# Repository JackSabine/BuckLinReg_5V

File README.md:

# Buck + Linear Regulator

Power supply for the Breadboard\_CPU.  This converter accepts input voltages 8 - 13 V and will output a regulated 5 V.

Tried to bodge a wire to measure a voltage without a testpoint...  Oops...

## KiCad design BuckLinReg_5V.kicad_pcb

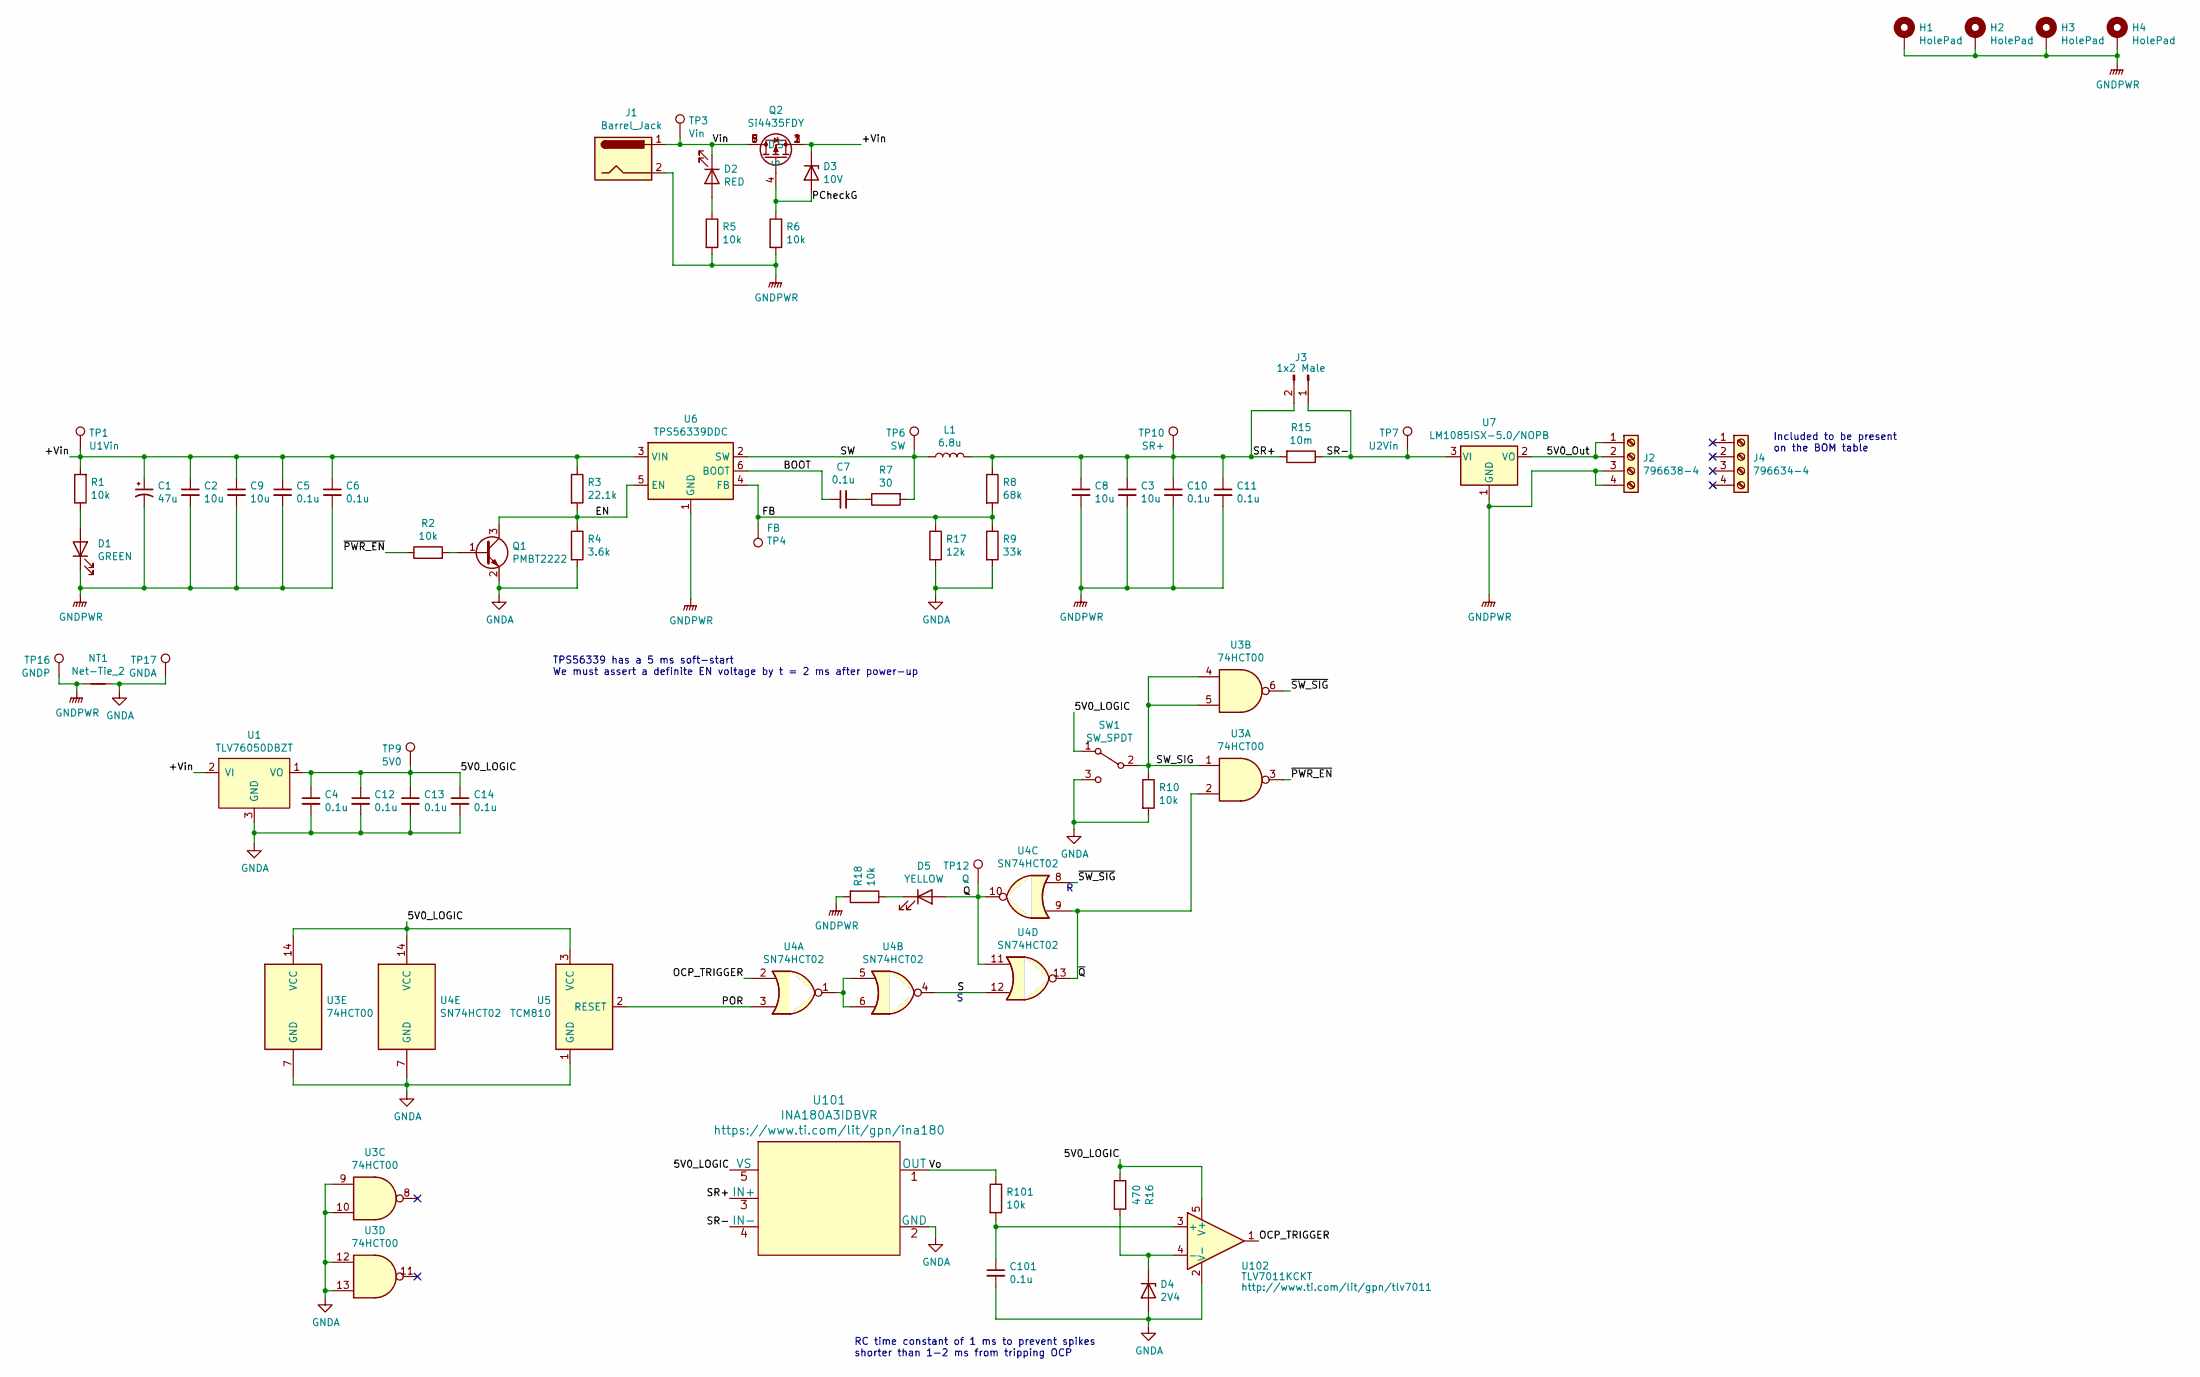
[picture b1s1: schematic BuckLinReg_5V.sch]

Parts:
C1: 47u; CP_Radial_D6.3mm_P2.50mm
C2, C3: 10u; C_1206_3216Metric_Pad1.33x1.80mm_HandSolder
C4, C6, C7, C11, C12, C13, C14, C101: 0.1u; C_0603_1608Metric_Pad1.08x0.95mm_HandSolder
C5, C10: 0.1u; C_0805_2012Metric_Pad1.18x1.45mm_HandSolder
C8, C9: 10u; C_1210_3225Metric_Pad1.33x2.70mm_HandSolder
D1: GREEN; D_1206_3216Metric_Pad1.42x1.75mm_HandSolder
D2: RED; D_1206_3216Metric_Pad1.42x1.75mm_HandSolder
D3: 10V; D_SOT-23_ANK
D4: 2V4; D_SOD-323_HandSoldering
D5: YELLOW; D_1206_3216Metric_Pad1.42x1.75mm_HandSolder
H1, H2, H3, H4: HolePad; ProjectBoxMountingHole_X001WPJR9N
J1: Barrel_Jack; BarrelJack_CUI_PJ-102AH_Horizontal
J2: 796638-4; 796636-4
J3: 1x2 Male; PinHeader_1x02_P2.54mm_Vertical
J4: 796634-4
L1: 6.8u; IHLP4040DZER6R8M8A
NT1: Net-Tie_2; NetShorter
Q1: PMBT2222; SOT-23_Handsoldering
Q2: Si4435FDY; SO-8_3.9x4.9mm_P1.27mm
R1, R2, R5, R6, R10, R18, R101: 10k; R_1206_3216Metric_Pad1.30x1.75mm_HandSolder
R3: 22.1k; R_1206_3216Metric_Pad1.30x1.75mm_HandSolder
R4: 3.6k; R_1206_3216Metric_Pad1.30x1.75mm_HandSolder
R7: 30; R_2010_5025Metric_Pad1.40x2.65mm_HandSolder
R8: 68k; R_1206_3216Metric_Pad1.30x1.75mm_HandSolder
R9: 33k; R_1206_3216Metric_Pad1.30x1.75mm_HandSolder
R15: 10m; R_1206_3216Metric_Pad1.30x1.75mm_HandSolder
R16: 470; R_1206_3216Metric_Pad1.30x1.75mm_HandSolder
R17: 12k; R_1206_3216Metric_Pad1.30x1.75mm_HandSolder
SW1: SW_SPDT; PinHeader_1x03_P2.54mm_Vertical
TP1: U1Vin; TestPoint_THTPad_D2.0mm_Drill1.0mm
TP3: Vin; TestPoint_THTPad_D2.0mm_Drill1.0mm
TP4: FB; TestPoint_THTPad_D2.0mm_Drill1.0mm
TP6: SW; TestPoint_THTPad_D2.0mm_Drill1.0mm
TP7: U2Vin; TestPoint_THTPad_D2.0mm_Drill1.0mm
TP9: 5V0; TestPoint_THTPad_D2.0mm_Drill1.0mm
TP10: SR+; TestPoint_THTPad_D2.0mm_Drill1.0mm
TP12: Q; TestPoint_THTPad_D2.0mm_Drill1.0mm
TP16: GNDP; TestPoint_THTPad_D2.0mm_Drill1.0mm
TP17: GNDA; TestPoint_THTPad_D2.0mm_Drill1.0mm
U1: TLV76050DBZT; SOT-23_Handsoldering
U3: 74HCT00; SOIC-14_3.9x8.7mm_P1.27mm
U4: SN74HCT02; SOIC-14_3.9x8.7mm_P1.27mm
U5: TCM810; SOT-23_Handsoldering
U6: TPS56339DDC; SOT-23-6
U7: LM1085ISX-5.0/NOPB; TO-263-3_TabPin2
U101: INA180A3IDBVR; SOT-23-5_HandSoldering
U102: TLV7011KCKT; SOT-23-5_HandSoldering

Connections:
/5V0_LOGIC: C4.1, C12.1, C13.1, C14.1, R16.1, SW1.1 (A), TP9.1, U1.1 (VO), U3.14 (VCC), U4.14 (VCC), U5.3 (VCC), U101.5 (VS), U102.5 (V+)
/5V0_Out: J2.1, J2.2, U7.2 (VO)
/+Vin: C1.1, C2.1, C5.1, C6.1, C9.1, D3.1 (K), Q2.1 (S), Q2.2 (S), Q2.3 (S), R1.2, R3.1, TP1.1, U1.2 (VI), U6.3 (VIN)
/BOOT: C7.1, U6.6 (BOOT)
/EN: Q1.3 (C), R3.2, R4.1, U6.5 (EN)
/FB: R8.2, R9.1, R17.1, TP4.1, U6.4 (FB)
/OCP_TRIGGER: U4.2, U102.1; also elsewhere on the board
/PCheckG: D3.2 (A), Q2.4 (G), R6.1
/POR: U4.3, U5.2 (RESET)
/Q: D5.2 (A), TP12.1, U4.10, U4.11
/S: U4.4, U4.12
/SR+: C3.1, C8.1, C10.1, C11.1, J3.2, L1.2, R8.1, R15.2, TP10.1, U101.3 (IN+)
/SR-: J3.1, R15.1, TP7.1, U7.3 (VI), U101.4 (IN-)
/SW: L1.1, R7.2, TP6.1, U6.2 (SW)
/SW_SIG: R10.1, SW1.2 (B), U3.1, U3.4, U3.5
/Vin: D2.1 (K), J1.1, Q2.5 (D), Q2.6 (D), Q2.7 (D), Q2.8 (D), TP3.1
/Vo: R101.1, U101.1 (OUT); also elsewhere on the board
/~PWR_EN: R2.1, U3.3
/~Q: U3.2, U4.9, U4.13
/~SW_SIG: U3.6, U4.8
GNDA: C4.2, C12.2, C13.2, C14.2, C101.2, D4.2 (A), NT1.2, Q1.2 (E), R4.2, R9.2, R10.2, R17.2, SW1.3 (C), TP17.1, U1.3 (GND), U3.7 (GND), U3.9, U3.10, U3.12, U3.13, U4.7 (GND), U5.1 (GND), U101.2 (GND), U102.2 (V-)
GNDPWR: C1.2, C2.2, C3.2, C5.2, C6.2, C8.2, C9.2, C10.2, C11.2, D1.1 (K), H1.1, H2.1, H3.1, H4.1, J1.2, J2.3, J2.4, NT1.1, R5.2, R6.2, R18.2, TP16.1, U6.1 (GND), U7.1 (GND)
unnamed: C7.2, R7.1
unnamed: C101.1, R101.2, U102.3 (+)
unnamed: D1.2 (A), R1.1
unnamed: D2.2 (A), R5.1
unnamed: D4.1 (K), R16.2, U102.4 (-)
unnamed: D5.1 (K), R18.1
unnamed: Q1.1 (B), R2.2
unnamed: U4.1, U4.5, U4.6

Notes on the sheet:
TPS56339 has a 5 ms soft-start We must assert a definite EN voltage by t = 2 ms after power-up
Included to be present on the BOM table
RC time constant of 1 ms to prevent spikes shorter than 1-2 ms from tripping OCP

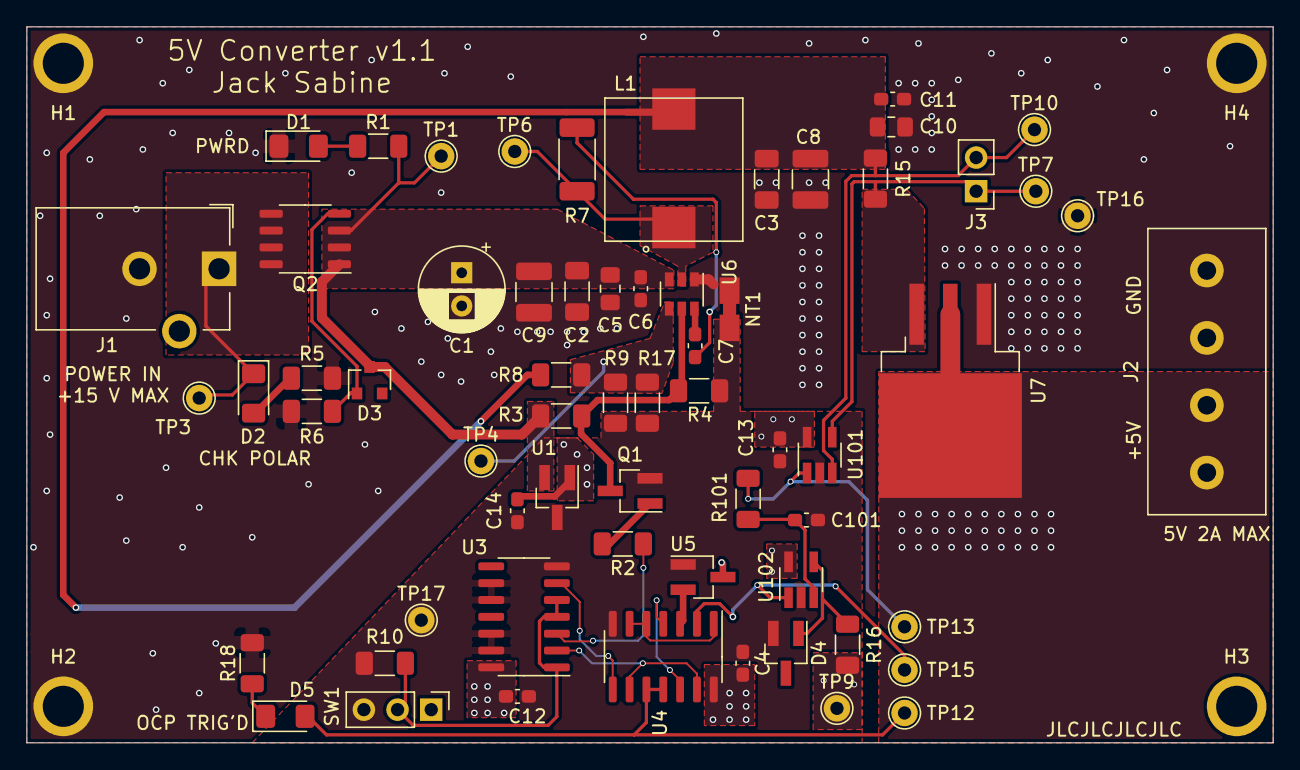
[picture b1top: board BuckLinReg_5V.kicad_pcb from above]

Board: 2 copper layers, 94.0 x 54.0 mm, 67 parts (0 on the bottom side), 30 nets.

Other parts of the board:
TP13: Iout; TestPoint_THTPad_D2.0mm_Drill1.0mm
TP15: OCPT; TestPoint_THTPad_D2.0mm_Drill1.0mm

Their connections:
/OCP_TRIGGER: TP15.1; also elsewhere on the board
/Vo: TP13.1; also elsewhere on the board

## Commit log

2021-02-05 Init
2021-02-06 Created .sch, selected parts, started PCB layout
2021-02-11 Added overcurrent protection circuit and assigned all MFPNs and footprints
2021-02-13 Two grounds: GNDA and pwrGND. Continued PCB dev.
2021-02-22 Simulated zener for different values R. Routed logic portion of board.
2021-02-23 Added testpoints and finished routing board
2021-02-26 Converted to 4-layer PCB. Minimum track width 0.25 mm.
2021-02-26 Redid vias and fixed silkscreen overlap
2021-02-27 Added new power barrier connector. Increased minimum copper to copper clearance to 0.21 mm.
2021-02-27 Moved some test points to allow for better ground high current return path
2021-03-01 Verified OCP switch logic in verilog
2021-03-22 PCB Ordered
2021-04-03 Begin rev. 2 sch and PCB resize to 94x54mm
2021-04-03 Completed initial layout of rev. 2
2021-04-05 Changed nettie and gnd clearances
2021-04-06 PCB v1.1 ordered
2021-12-08 Prettifying schematic
2022-09-12 Added pictures to README
